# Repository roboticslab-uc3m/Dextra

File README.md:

# Dextra

Dextra is a printable robotic hand with the size of a human hand. This project was initially started by A. Villoslada to build a replicable and low cost alternative to current robotic hand prostheses. However, I think this device has more potential uses, for example in robotics research (humanoid robotics, mobile platforms with manipulation capabilities) or in education, fields that could benefit from the existence of a cheap and easy to repair robotic hand, a robotic device that is replicable and hackable, and simple but functional.

There is more information about Dextra on its [hackaday.io project page](https://hackaday.io/project/9890-dextra).

## Dextra TPMG90

J. Gago Industrial Technologies Engineering Bachelor's Degree Final Project comprises the development and integration of an anthropomorphic robotic hand in the humanoid robot TEO. TEO is a household companion developed by RoboticsLab, at Carlos III University of Madrid, whose current robotic hands lack the necessary functionality for the tasks that require high manual dexterity, like fabric manipulation.

The scope of the proposed objectives is achieved through the development and study of several versions of the selected hand at the mechanical, electronic and software level. Multiple experiments are developed to evaluate the effectiveness of the robotic hand. In addition, the regulatory technical framework and the socio-economic environment of the project are evaluated, so that it complies satisfactorily with the established restrictions and adjusts to the current social and economic context.

The project is oriented to numerous additional studies around their behavior in the humanoid, contemplating the expansion of the TEO functions in relation to the versatility provided by his new fully functional hands.

## Dextra TPMG90S

Miguel Alache Manchado followed up on Jennifer Gago's work in his Bachelor's Degree Final Project (Industrial Electronics Engineering and Automation), notably improving the 3D CAD and PCB designs. This iteration is dubbed TPMG90S due to the replacement of the TPMG90 servomotor with this new model.

Although compatibility with TEO is preserved, the aim was to mount this hand on the ABB CRB 15000-5 "GoFa" collaborative robot arm.

## Useful documents

The assembly instructions for the original Dextra can be found [here](doc/dextra_assembly_instructions.pdf).

## Project index

* [CAD](CAD) - Printable parts
* [Control](Control) - Code for different control methods (EMG, GUI)
* [doc](doc) - Documentation files
* [Firmware](Firmware) - Main program and libraries that make Dextra move
* [PCB](PCB) - PCB design files
* [Schematics](Schematics) - Electronic schematics of Dextra Original, TPMG90-1 and TPMG90-2

## License

Code is licensed under the [GPL v3 License](https://www.gnu.org/licenses/gpl-3.0.html). The rest of the work is licensed under the [Creative Commons Attribution-ShareAlike 4.0 International License](http://creativecommons.org/licenses/by-sa/4.0/).

## See also

* [dextra-yarp-devices](https://github.com/roboticslab-uc3m/dextra-yarp-devices) - YARP plugins for Dextra control board

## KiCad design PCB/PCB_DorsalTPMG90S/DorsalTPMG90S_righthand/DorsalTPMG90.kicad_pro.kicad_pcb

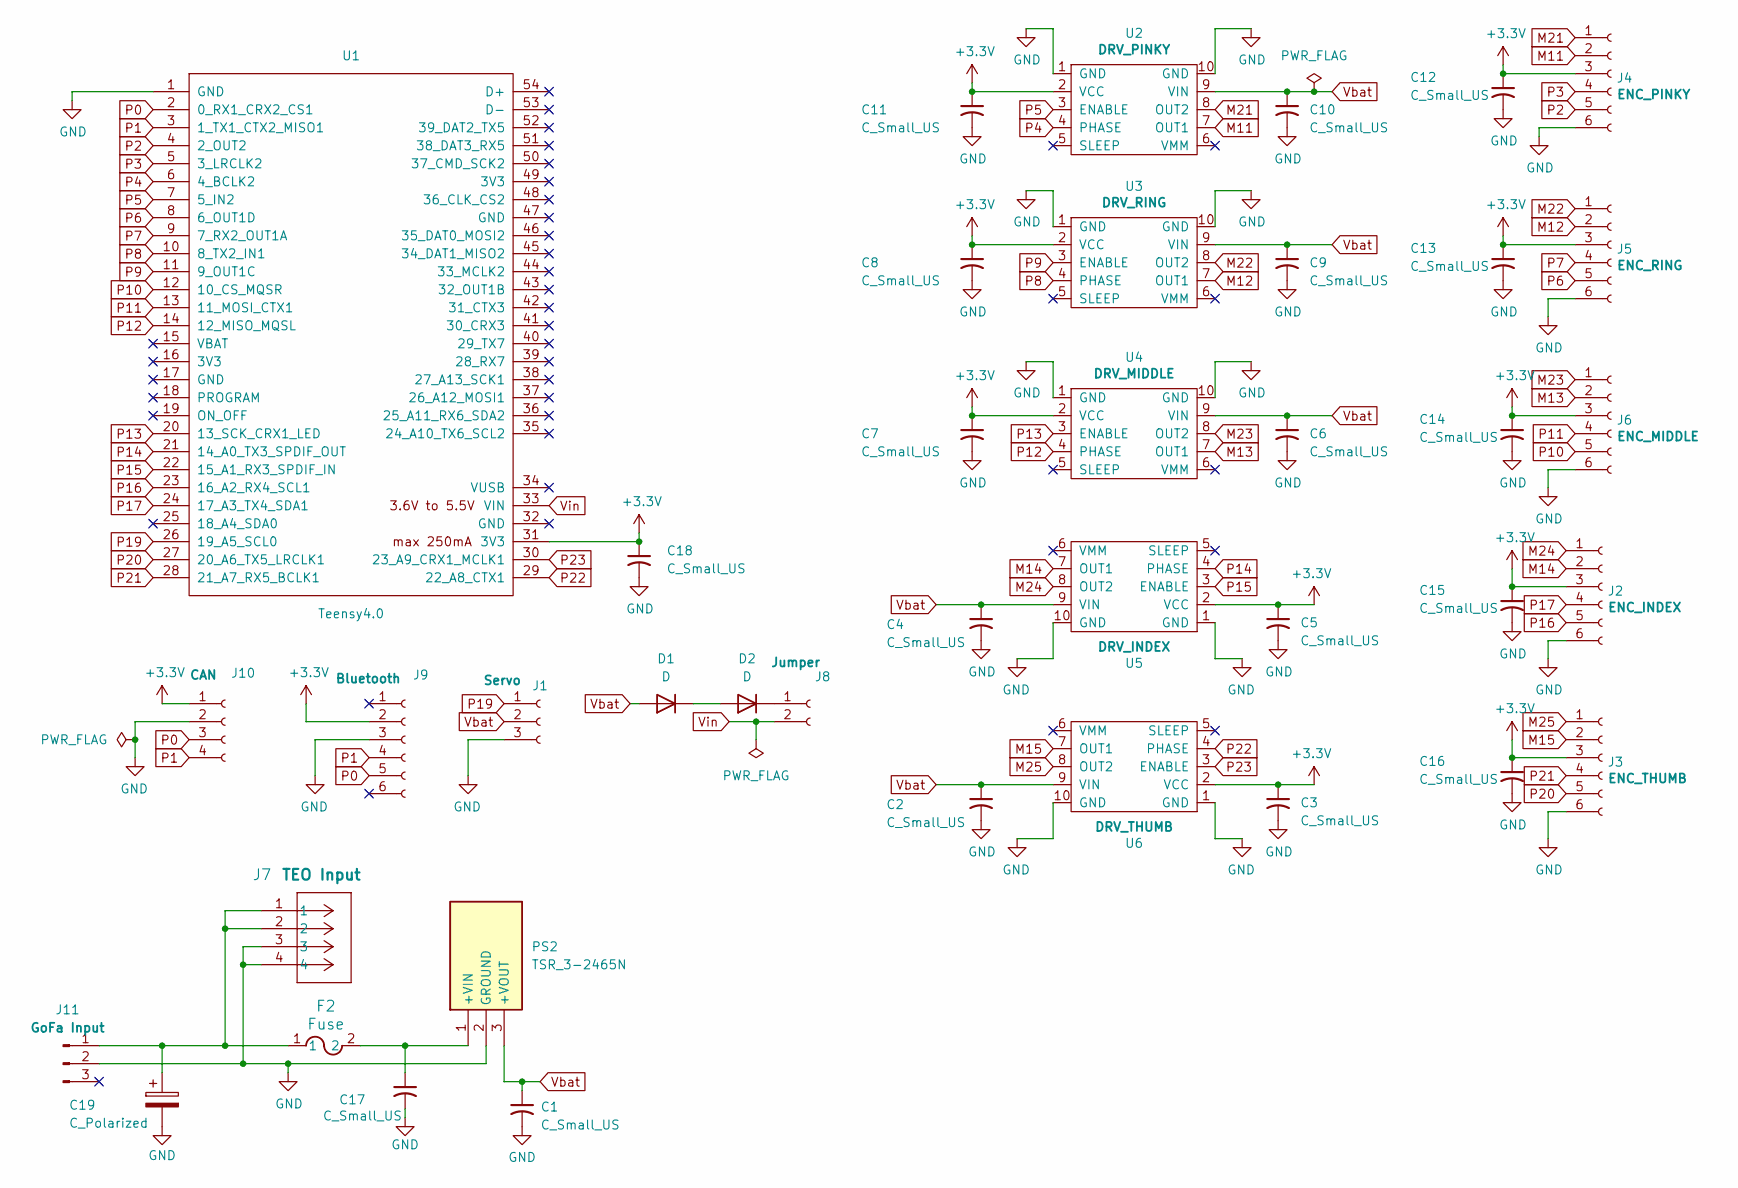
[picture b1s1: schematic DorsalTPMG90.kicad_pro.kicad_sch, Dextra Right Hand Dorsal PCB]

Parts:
C1, C2, C3, C4, C5, C6, C7, C8, C9, C10, C11, C12, C13, C14, C15, C16, C18: C_Small_US; C_0603_1608Metric
C17: C_Small_US; C_0805_2012Metric
C19: C_Polarized; Cin
D1, D2: D; D_SOD-123
F2: Fuse; FUSE_560_1009_LTF
J1: Servo; PinHeader_1x03_P2.54mm_Vertical
J2: ENC_INDEX; PinHeader_1x06_P2.54mm_Vertical
J3: ENC_THUMB; PinHeader_1x06_P2.54mm_Vertical
J4: ENC_PINKY; PinHeader_1x06_P2.54mm_Vertical
J5: ENC_RING; PinHeader_1x06_P2.54mm_Vertical
J6: ENC_MIDDLE; PinHeader_1x06_P2.54mm_Vertical
J7: TEO Input; conector_Molex_2x2
J8: Jumper; PinHeader_1x02_P2.54mm_Vertical
J9: Bluetooth; PinHeader_1x06_P2.54mm_Vertical
J10: CAN; PinHeader_1x04_P2.54mm_Vertical
J11: GoFa Input; PinHeader_1x03_P2.54mm_Vertical
PS2: TSR_3-2465N; TSR32465N; Manufacturer_Part_Number TSR 3-2465N
U1: Teensy4.0; Teensy40_SidesOnly
U2: DRV_PINKY; Pololu_DRV8838
U3: DRV_RING; Pololu_DRV8838
U4: DRV_MIDDLE; Pololu_DRV8838
U5: DRV_INDEX; Pololu_DRV8838
U6: DRV_THUMB; Pololu_DRV8838

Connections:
+3.3V: C3.1, C5.1, C7.1, C8.1, C11.1, C12.1, C13.1, C14.1, C15.1, C16.1, C18.1, J2.3, J3.3, J4.3, J5.3, J6.3, J9.2, J10.1, U1.31 (3V3), U2.2 (VCC), U3.2 (VCC), U4.2 (VCC), U5.2 (VCC), U6.2 (VCC)
GND: C1.2, C2.2, C3.2, C4.2, C5.2, C6.2, C7.2, C8.2, C9.2, C10.2, C11.2, C12.2, C13.2, C14.2, C15.2, C16.2, C17.2, C18.2, C19.2, J1.3, J2.6, J3.6, J4.6, J5.6, J6.6, J7.3, J7.4, J9.3, J10.2, J11.2, PS2.2 (GROUND), U1.1 (GND), U2.1 (GND), U2.10 (GND), U3.1 (GND), U3.10 (GND), U4.1 (GND), U4.10 (GND), U5.1 (GND), U5.10 (GND), U6.1 (GND), U6.10 (GND)
M11: J4.2, U2.7 (OUT1)
M12: J5.2, U3.7 (OUT1)
M13: J6.2, U4.7 (OUT1)
M14: J2.2, U5.7 (OUT1)
M15: J3.2, U6.7 (OUT1)
M21: J4.1, U2.8 (OUT2)
M22: J5.1, U3.8 (OUT2)
M23: J6.1, U4.8 (OUT2)
M24: J2.1, U5.8 (OUT2)
M25: J3.1, U6.8 (OUT2)
unnamed: D1.1 (K), D2.2 (A)
unnamed: D2.1 (K), J8.1
unnamed: C19.1, F2.1, J7.1, J7.2, J11.1
unnamed: C17.1, F2.2, PS2.1 (+VIN)
P0: J9.5, J10.3, U1.2 (0_RX1_CRX2_CS1)
P1: J9.4, J10.4, U1.3 (1_TX1_CTX2_MISO1)
P2: J4.5, U1.4 (2_OUT2)
P3: J4.4, U1.5 (3_LRCLK2)
P4: U1.6 (4_BCLK2), U2.4 (PHASE)
P5: U1.7 (5_IN2), U2.3 (ENABLE)
P6: J5.5, U1.8 (6_OUT1D)
P7: J5.4, U1.9 (7_RX2_OUT1A)
P8: U1.10 (8_TX2_IN1), U3.4 (PHASE)
P9: U1.11 (9_OUT1C), U3.3 (ENABLE)
P10: J6.5, U1.12 (10_CS_MQSR)
P11: J6.4, U1.13 (11_MOSI_CTX1)
P12: U1.14 (12_MISO_MQSL), U4.4 (PHASE)
P13: U1.20 (13_SCK_CRX1_LED), U4.3 (ENABLE)
P14: U1.21 (14_A0_TX3_SPDIF_OUT), U5.4 (PHASE)
P15: U1.22 (15_A1_RX3_SPDIF_IN), U5.3 (ENABLE)
P16: J2.5, U1.23 (16_A2_RX4_SCL1)
P17: J2.4, U1.24 (17_A3_TX4_SDA1)
P19: J1.1, U1.26 (19_A5_SCL0)
P20: J3.5, U1.27 (20_A6_TX5_LRCLK1)
P21: J3.4, U1.28 (21_A7_RX5_BCLK1)
P22: U1.29 (22_A8_CTX1), U6.4 (PHASE)
P23: U1.30 (23_A9_CRX1_MCLK1), U6.3 (ENABLE)
Vbat: C1.1, C2.1, C4.1, C6.1, C9.1, C10.1, D1.2 (A), J1.2, PS2.3 (+VOUT), U2.9 (VIN), U3.9 (VIN), U4.9 (VIN), U5.9 (VIN), U6.9 (VIN)
Vin: J8.2, U1.33 (VIN)

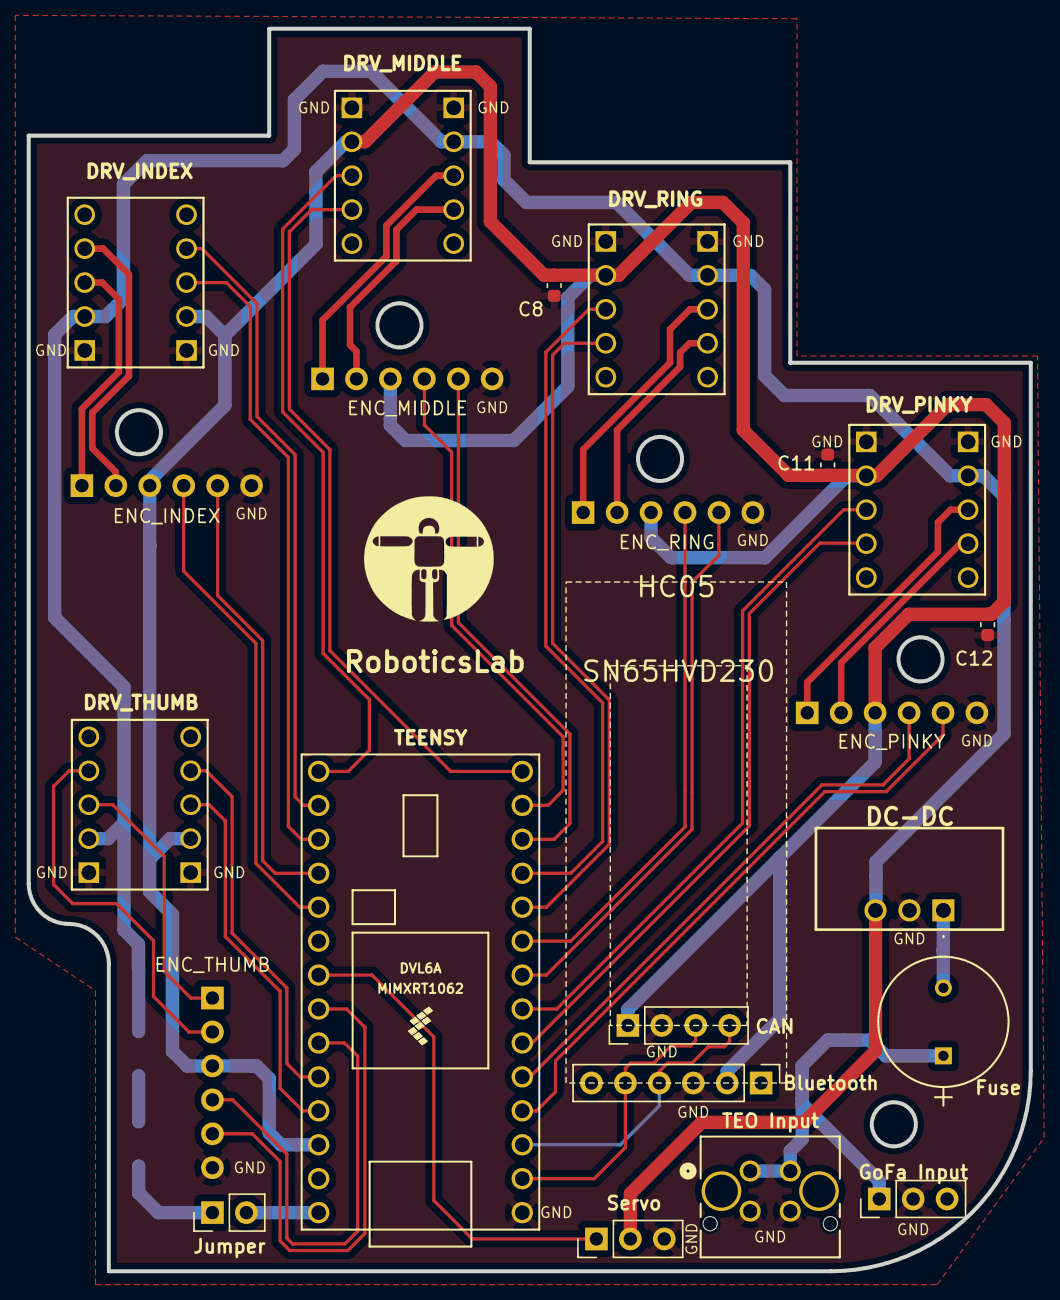
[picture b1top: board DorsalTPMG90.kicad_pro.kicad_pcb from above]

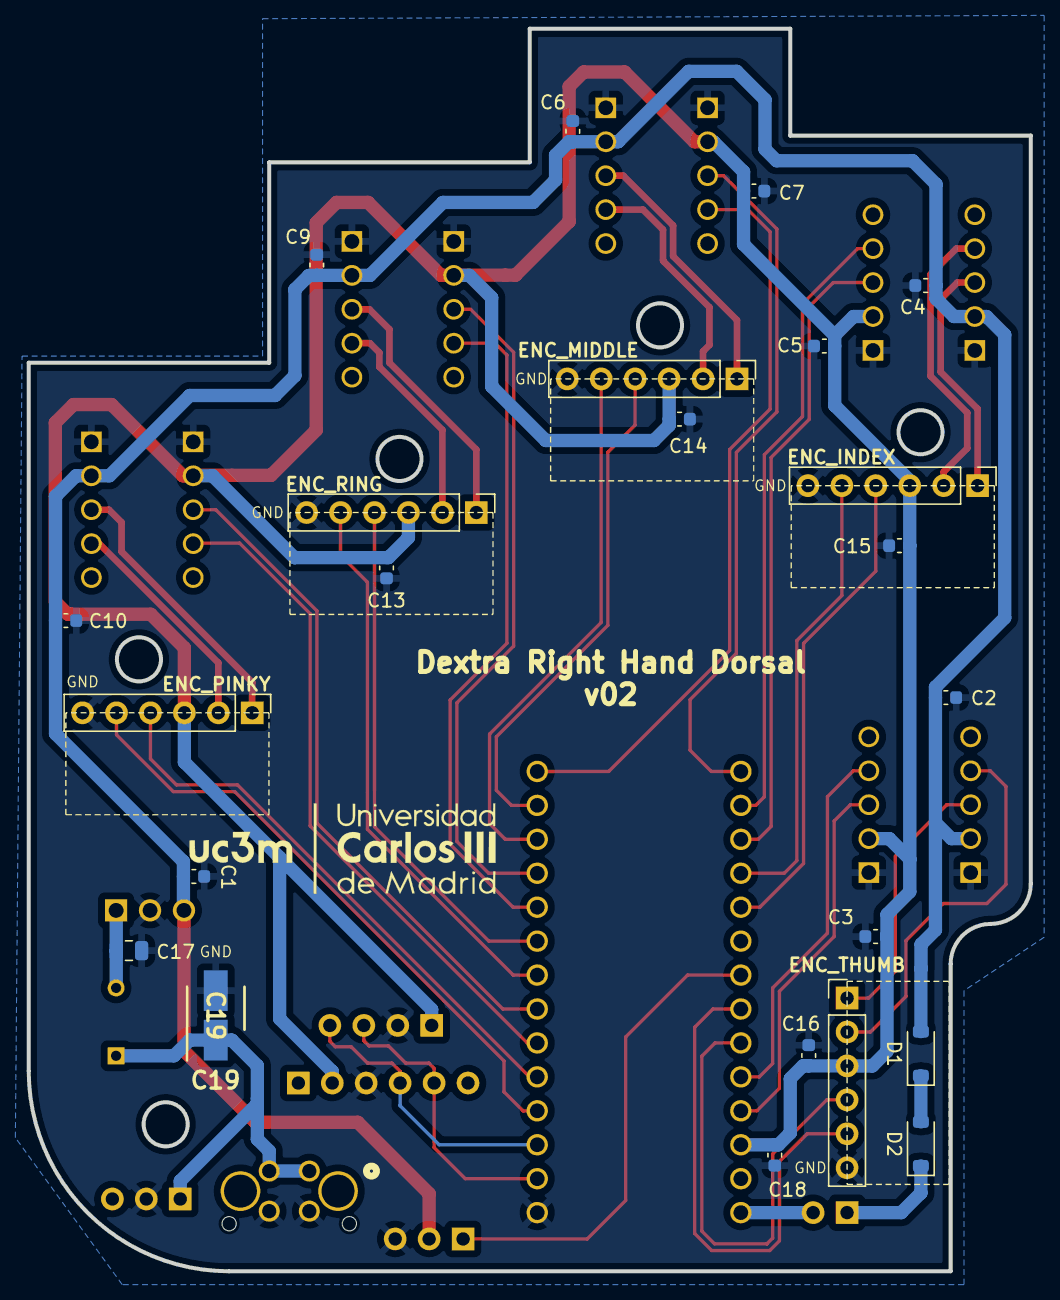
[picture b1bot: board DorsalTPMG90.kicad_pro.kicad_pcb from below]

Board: 2 copper layers, 75.0 x 93.0 mm, 40 parts (23 on the bottom side), 40 nets.

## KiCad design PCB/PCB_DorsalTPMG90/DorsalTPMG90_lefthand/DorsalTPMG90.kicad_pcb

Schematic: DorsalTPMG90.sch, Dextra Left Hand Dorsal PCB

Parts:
J1: Servo; PinHeader_1x03_P2.54mm_Vertical
J2: ENC_INDEX; PinHeader_1x06_P2.54mm_Vertical
J3: ENC_THUMB; PinHeader_1x06_P2.54mm_Vertical
J4: ENC_PINKY; PinHeader_1x06_P2.54mm_Vertical
J5: ENC_RING; PinHeader_1x06_P2.54mm_Vertical
J6: ENC_MIDDLE; PinHeader_1x06_P2.54mm_Vertical
J7: Baterry Input; PinHeader_1x02_P2.54mm_Vertical
U1: Teensy3.1; Teensy31_32_SidesOnly
U2: DRV_PINKY; Pololu_DRV8838
U3: DRV_RING; Pololu_DRV8838
U4: DRV_MIDDLE; Pololu_DRV8838
U5: DRV_INDEX; Pololu_DRV8838
U6: DRV_THUMB; Pololu_DRV8838

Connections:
+3V3: J2.3, J3.3, J4.3, J5.3, J6.3, U1.31 (3.3V_max100mA), U2.2 (VCC), U3.2 (VCC), U4.2 (VCC), U5.2 (VCC), U6.2 (VCC)
GND: J1.3, J2.6, J3.6, J4.6, J5.6, J6.6, J7.2, U1.1 (GND), U2.1 (GND), U2.10 (GND), U3.1 (GND), U3.10 (GND), U4.1 (GND), U4.10 (GND), U5.1 (GND), U5.10 (GND), U6.1 (GND), U6.10 (GND)
M11: J4.1, U2.7 (OUT1)
M12: J5.1, U3.7 (OUT1)
M13: J6.1, U4.7 (OUT1)
M14: J2.1, U5.7 (OUT1)
M15: J3.1, U6.7 (OUT1)
M21: J4.2, U2.8 (OUT2)
M22: J5.2, U3.8 (OUT2)
M23: J6.2, U4.8 (OUT2)
M24: J2.2, U5.8 (OUT2)
M25: J3.2, U6.8 (OUT2)
P0: J1.1, U1.2 (0_RX1_Touch)
P1: U1.3 (1_TX1_Touch), U6.3 (ENABLE)
P2: U1.4 (2_CS), U6.4 (PHASE)
P5: U1.7 (5_TX1_PWM), U5.3 (ENABLE)
P6: U1.8 (6_CS_PWM), U4.3 (ENABLE)
P7: U1.9 (7_RX3_DOUT), U5.4 (PHASE)
P8: U1.10 (8_TX3_DIN), U4.4 (PHASE)
P9: U1.11 (9_RX2_CS_PWM), U3.3 (ENABLE)
P10: U1.12 (10_TX2_CS_PWM), U2.3 (ENABLE)
P11: U1.13 (11_DOUT), U3.4 (PHASE)
P12: U1.14 (12_DIN), U2.4 (PHASE)
P14: J4.5, U1.21 (14_A0_SCK)
P15: J4.4, U1.22 (15_A1_CS_Touch)
P16: J5.5, U1.23 (16_A2_SCL0_Touch)
P17: J5.4, U1.24 (17_A3_SDA0_Touch)
P18: J6.5, U1.25 (18_A4_SDA0_Touch)
P19: J6.4, U1.26 (19_A5_SCL0_Touch)
P20: J2.5, U1.27 (20_A6_CS_PWM)
P21: J2.4, U1.28 (21_A7_RX1_CS_PWM)
P22: J3.5, U1.29 (22_A8_Touch_CS_PWM)
P23: J3.4, U1.30 (23_A9_Touch_CS_PWM)
Vbat: J1.2, J7.1, U2.9 (VIN), U3.9 (VIN), U4.9 (VIN), U5.9 (VIN), U6.9 (VIN)

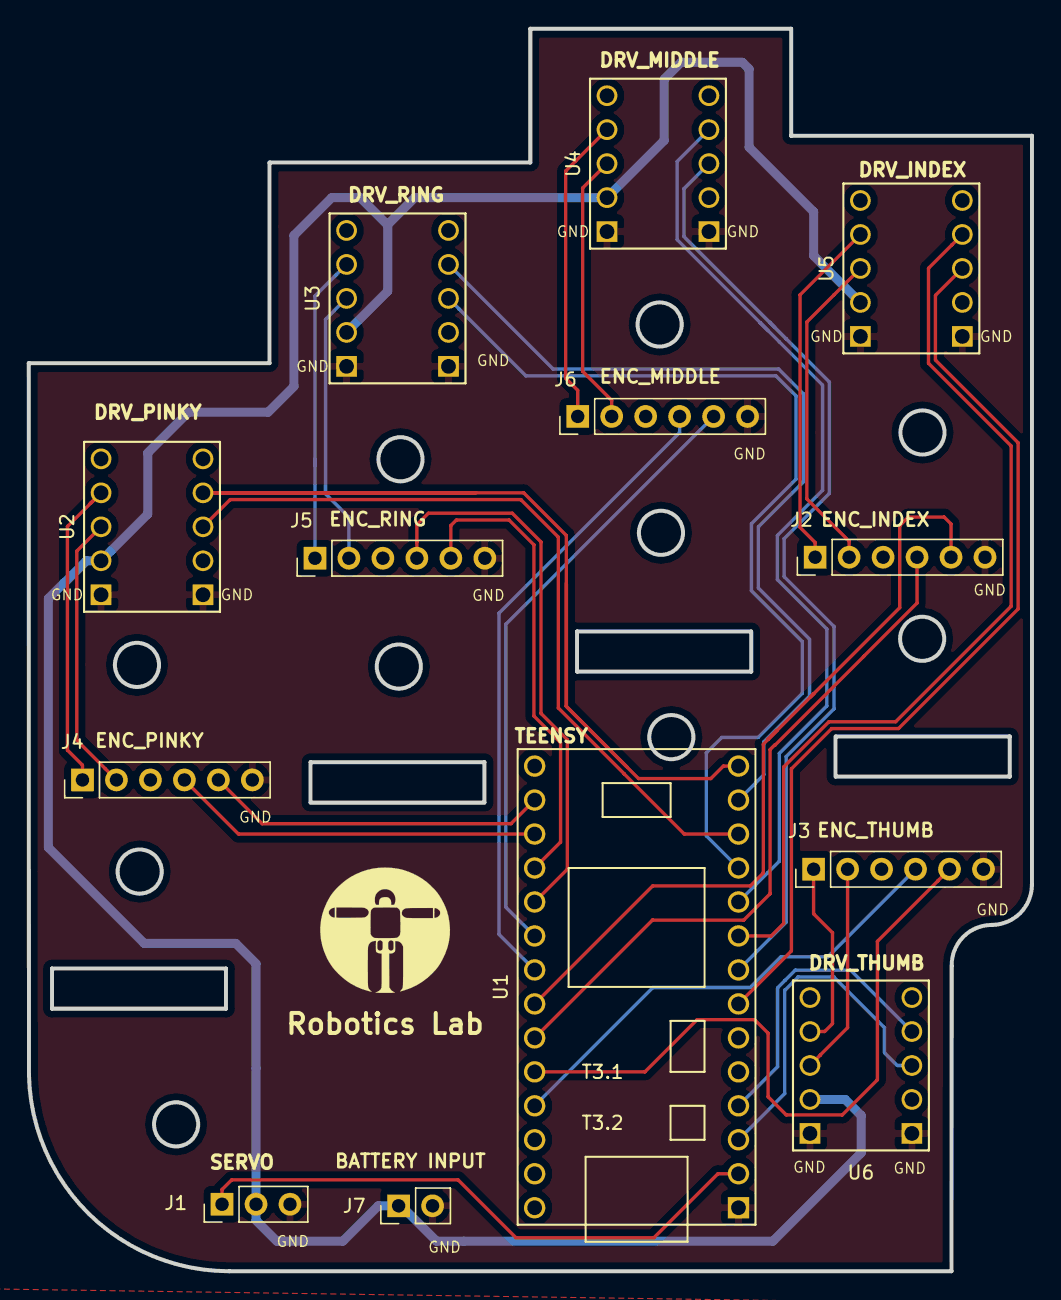
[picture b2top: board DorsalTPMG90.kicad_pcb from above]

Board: 2 copper layers, 75.0 x 92.9 mm, 13 parts (0 on the bottom side), 34 nets.

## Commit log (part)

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2018-03-05 Dextra TPMG90-1 CAD files
    Modified CAD files from original Dextra robotic hand files to adapt them to TowerPro MG90 servomotor
2018-07-01 Dextra TPMG90-2 CAD files
2018-07-01 Create Schematics
2018-07-01 DEXTRA Schematics
2018-07-01 Left hand CAD files
2018-07-01 Dextra ORIGINAL CAD files
2018-07-01 TEO & DEXTRA TPMG90-2
2018-07-01 TEO humanoid tasks
2018-07-01 README.md
2018-07-01 Cutkosky taxonomy
2018-07-01 Cutkosky taxonomy - Dextra TPMG90-2
2018-10-10 add missing file
2018-10-10 add more missing file
2019-03-06 photos
2019-03-06 readme
2019-06-27 Adjust pinout to new PCB
2019-06-27 Add udev rules
    https://www.pjrc.com/teensy/tutorial.html
2019-06-27 Adjust encoder limits and initial pose
2019-10-20 Add nested .gitignore generated by VS code
2021-12-03 title format change
2026-04-14 Embrace bytearray in modern pySerial, fix style
